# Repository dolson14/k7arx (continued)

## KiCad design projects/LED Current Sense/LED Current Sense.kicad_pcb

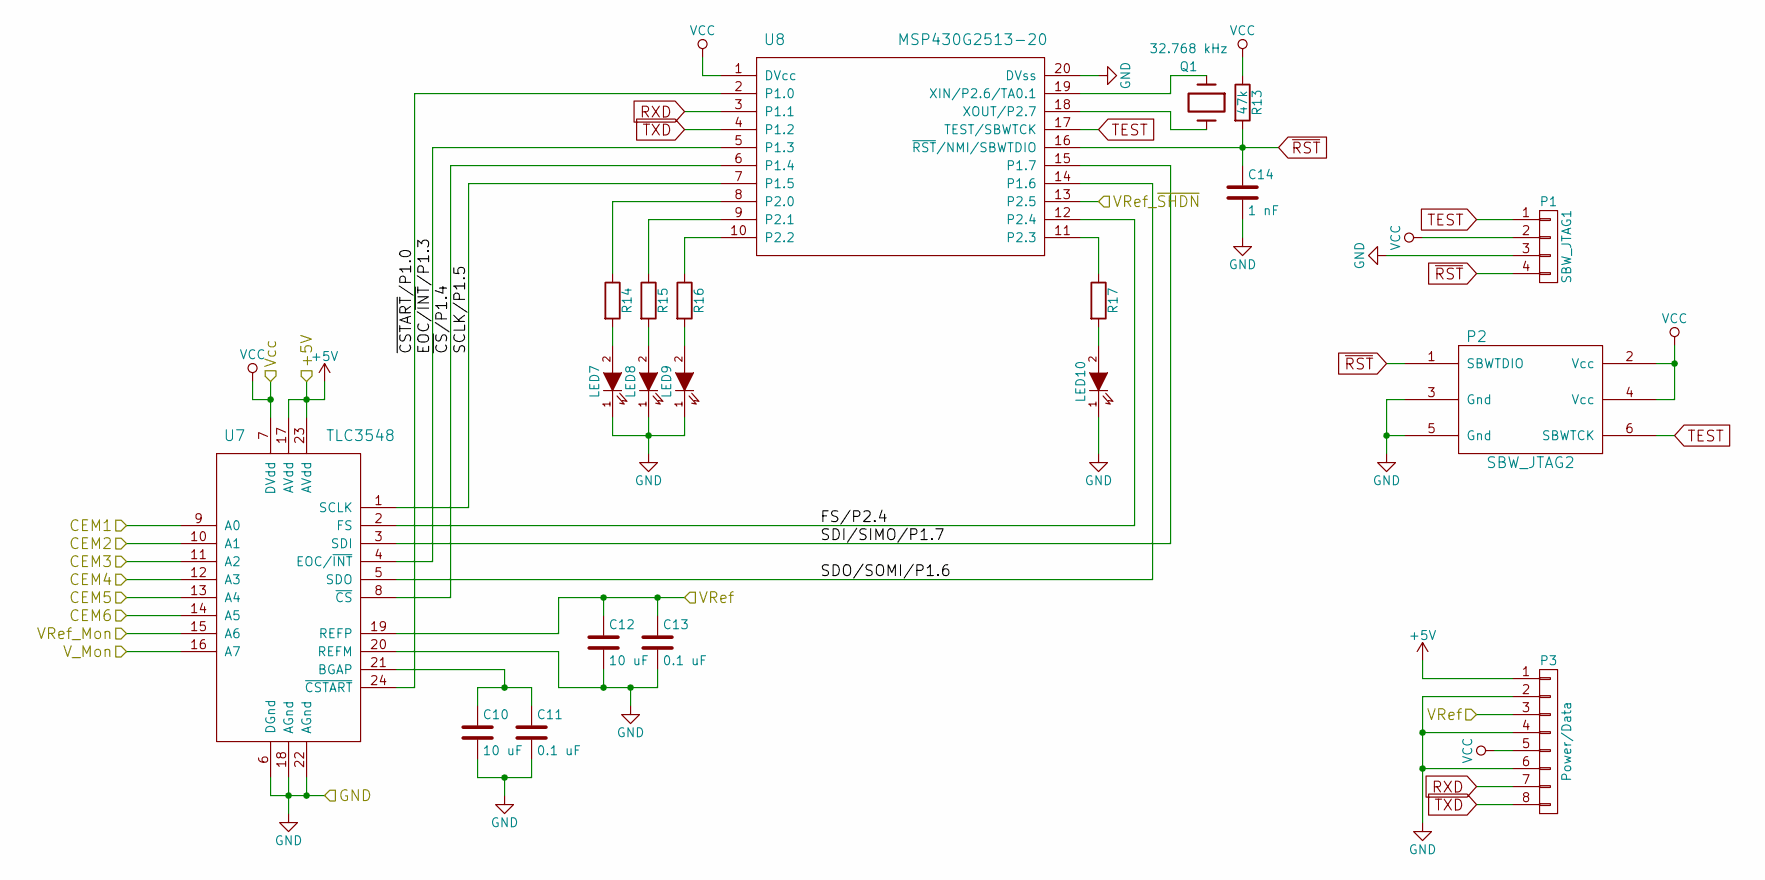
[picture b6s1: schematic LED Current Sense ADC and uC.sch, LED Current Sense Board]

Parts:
C10, C12: 10 uF; C_1206_HandSoldering
C11, C13: 0.1 uF; C_1206_HandSoldering
C14: 1 nF; C_1206_HandSoldering
LED7, LED8, LED9, LED10: LED-0805
P1: SBW_JTAG1; Pin_Header_Straight_1x04
P2: SBW_JTAG2; TC2030-MCP-FP
P3: Power/Data; Pin_Header_Straight_1x08
Q1: 32.768 kHz; Crystal_Round_Vertical_2mm
R13: 47k; R_1206_HandSoldering
R14, R15, R16, R17: R_1206_HandSoldering
U7: TLC3548; SOIC-24_7.5x15.4mm_Pitch1.27mm
U8: MSP430G2513-20; TSSOP-20_4.4x6.5mm_Pitch0.65mm

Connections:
+5V: P3.1, U7.17 (AVdd), U7.23 (AVdd); also elsewhere on the board
/ADC and Microcontroller/EOC/~INT~/P1.3: U7.4 (EOC/~INT), U8.5 (P1.3)
/ADC and Microcontroller/FS/P2.4: U7.2 (FS), U8.12 (P2.4)
/ADC and Microcontroller/SCLK/P1.5: U7.1 (SCLK), U8.7 (P1.5)
/ADC and Microcontroller/SDI/SIMO/P1.7: U7.3 (SDI), U8.15 (P1.7)
/ADC and Microcontroller/SDO/SOMI/P1.6: U7.5 (SDO), U8.14 (P1.6)
/ADC and Microcontroller/VRef: C12.1, C13.1, P3.3, U7.19 (REFP); also elsewhere on the board
/ADC and Microcontroller/~CSTART~/P1.0: U7.24 (~CSTART), U8.2 (P1.0)
/ADC and Microcontroller/~CS~/P1.4: U7.8 (~CS), U8.6 (P1.4)
/High Voltage Interface and Power System/A0: U7.9 (A0); also elsewhere on the board
/High Voltage Interface and Power System/A1: U7.10 (A1); also elsewhere on the board
/High Voltage Interface and Power System/A2: U7.11 (A2); also elsewhere on the board
/High Voltage Interface and Power System/A3: U7.12 (A3); also elsewhere on the board
/High Voltage Interface and Power System/A4: U7.13 (A4); also elsewhere on the board
/High Voltage Interface and Power System/A5: U7.14 (A5); also elsewhere on the board
/High Voltage Interface and Power System/A6: U7.15 (A6); also elsewhere on the board
/High Voltage Interface and Power System/A7: U7.16 (A7); also elsewhere on the board
/High Voltage Interface and Power System/P2.5: U8.13 (P2.5); also elsewhere on the board
GND: C10.2, C11.2, C12.2, C13.2, C14.2, LED7.1 (K), LED8.1 (K), LED9.1 (K), LED10.1 (K), P1.3, P2.3 (Gnd), P2.5 (Gnd), P3.2, P3.4, P3.6, U7.6 (DGnd), U7.18 (AGnd), U7.20 (REFM), U7.22 (AGnd), U8.20 (DVss); also elsewhere on the board
unnamed: C10.1, C11.1, U7.21 (BGAP)
unnamed: LED7.2 (A), R14.2
unnamed: LED8.2 (A), R15.2
unnamed: LED9.2 (A), R16.2
unnamed: LED10.2 (A), R17.2
unnamed: Q1.1, U8.19 (XIN/P2.6/TA0.1)
unnamed: Q1.2, U8.18 (XOUT/P2.7)
unnamed: R14.1, U8.8 (P2.0)
unnamed: R15.1, U8.9 (P2.1)
unnamed: R16.1, U8.10 (P2.2)
unnamed: R17.1, U8.11 (P2.3)
RXD: P3.7, U8.3 (P1.1)
TEST: P1.1, P2.6 (SBWTCK), U8.17 (TEST/SBWTCK)
TXD: P3.8, U8.4 (P1.2)
VCC: P1.2, P2.2 (Vcc), P2.4 (Vcc), P3.5, R13.1, U7.7 (DVdd), U8.1 (DVcc); also elsewhere on the board
~RST: C14.1, P1.4, P2.1 (SBWTDIO), R13.2, U8.16 (~RST~/NMI/SBWTDIO)

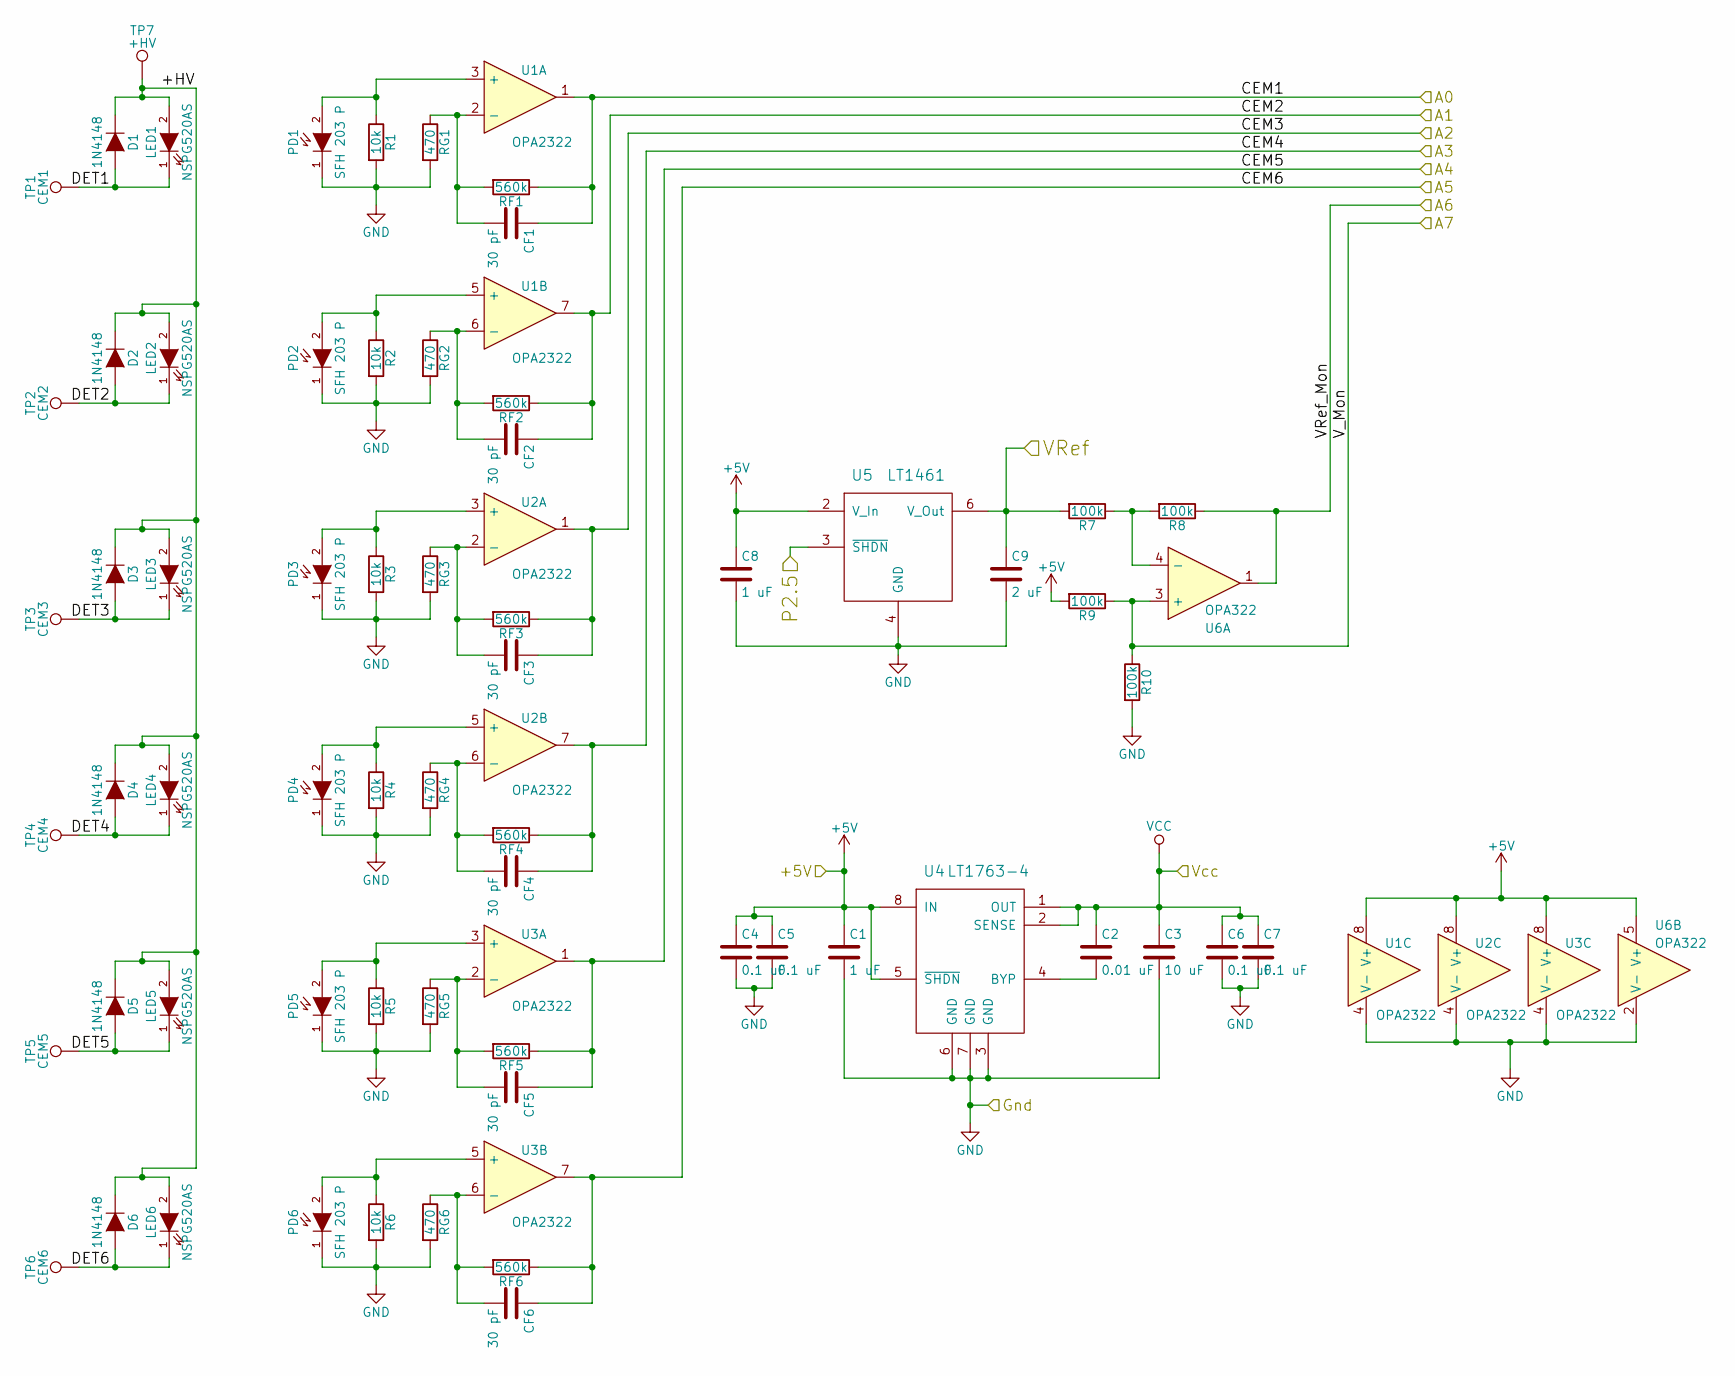
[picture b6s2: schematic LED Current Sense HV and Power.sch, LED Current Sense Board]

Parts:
C1, C8: 1 uF; C_1206_HandSoldering
C2: 0.01 uF; C_1206_HandSoldering
C3: 10 uF; C_1206_HandSoldering
C4, C5, C6, C7: 0.1 uF; C_1206_HandSoldering
C9: 2 uF; C_1206_HandSoldering
CF1, CF2, CF3, CF4, CF5, CF6: 30 pF; C_1206_HandSoldering
D1, D2, D3, D4, D5, D6: 1N4148; Diode_DO-35_SOD27_Horizontal_RM10
LED1, LED2, LED3, LED4, LED5, LED6: NSPG520AS; LED-5MM
PD1, PD2, PD3, PD4, PD5, PD6: SFH 203 P; LED-5MM
R1, R2, R3, R4, R5, R6: 10k; R_1206_HandSoldering
R7, R8, R9, R10: 100k; R_1206_HandSoldering
RF1, RF2, RF3, RF4, RF5, RF6: 560k; R_1206_HandSoldering
RG1, RG2, RG3, RG4, RG5, RG6: 470; R_1206_HandSoldering
TP1: CEM1; No.2N
TP2: CEM2; No.2N
TP3: CEM3; No.2N
TP4: CEM4; No.2N
TP5: CEM5; No.2N
TP6: CEM6; No.2N
TP7: +HV; No.2N
U1, U2, U3: OPA2322; SOIC-8_3.9x4.9mm_Pitch1.27mm
U4: LT1763-4; SOIC-8_3.9x4.9mm_Pitch1.27mm
U5: LT1461; SOIC-8_3.9x4.9mm_Pitch1.27mm
U6: OPA322; SOT-23-5

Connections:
+5V: C1.1, C4.1, C5.1, C8.1, R9.2, U1.8 (V+), U2.8 (V+), U3.8 (V+), U4.5 (~SHDN), U4.8 (IN), U5.2 (V_In), U6.5 (V+); also elsewhere on the board
/ADC and Microcontroller/VRef: C9.1, R7.2, U5.6 (V_Out); also elsewhere on the board
/High Voltage Interface and Power System/+HV: D1.1 (K), D2.1 (K), D3.1 (K), D4.1 (K), D5.1 (K), D6.1 (K), LED1.2 (A), LED2.2 (A), LED3.2 (A), LED4.2 (A), LED5.2 (A), LED6.2 (A), TP7.1
/High Voltage Interface and Power System/A0: CF1.1, RF1.1, U1.1; also elsewhere on the board
/High Voltage Interface and Power System/A1: CF2.1, RF2.1, U1.7; also elsewhere on the board
/High Voltage Interface and Power System/A2: CF3.1, RF3.1, U2.1; also elsewhere on the board
/High Voltage Interface and Power System/A3: CF4.1, RF4.1, U2.7; also elsewhere on the board
/High Voltage Interface and Power System/A4: CF5.1, RF5.1, U3.1; also elsewhere on the board
/High Voltage Interface and Power System/A5: CF6.1, RF6.1, U3.7; also elsewhere on the board
/High Voltage Interface and Power System/A6: R8.1, U6.1; also elsewhere on the board
/High Voltage Interface and Power System/A7: R9.1, R10.1, U6.3 (+); also elsewhere on the board
/High Voltage Interface and Power System/P2.5: U5.3 (~SHDN); also elsewhere on the board
GND: C1.2, C3.2, C4.2, C5.2, C6.2, C7.2, C8.2, C9.2, PD1.1 (K), PD2.1 (K), PD3.1 (K), PD4.1 (K), PD5.1 (K), PD6.1 (K), R1.2, R2.2, R3.2, R4.2, R5.2, R6.2, R10.2, RG1.2, RG2.2, RG3.2, RG4.2, RG5.2, RG6.2, U1.4 (V-), U2.4 (V-), U3.4 (V-), U4.3 (GND), U4.6 (GND), U4.7 (GND), U5.4 (GND), U6.2 (V-); also elsewhere on the board
unnamed: C2.2, U4.4 (BYP)
unnamed: CF1.2, RF1.2, RG1.1, U1.2 (-)
unnamed: CF2.2, RF2.2, RG2.1, U1.6 (-)
unnamed: CF3.2, RF3.2, RG3.1, U2.2 (-)
unnamed: CF4.2, RF4.2, RG4.1, U2.6 (-)
unnamed: CF5.2, RF5.2, RG5.1, U3.2 (-)
unnamed: CF6.2, RF6.2, RG6.1, U3.6 (-)
unnamed: D1.2 (A), LED1.1 (K), TP1.1
unnamed: D2.2 (A), LED2.1 (K), TP2.1
unnamed: D3.2 (A), LED3.1 (K), TP3.1
unnamed: D4.2 (A), LED4.1 (K), TP4.1
unnamed: D5.2 (A), LED5.1 (K), TP5.1
unnamed: D6.2 (A), LED6.1 (K), TP6.1
unnamed: PD1.2 (A), R1.1, U1.3 (+)
unnamed: PD2.2 (A), R2.1, U1.5 (+)
unnamed: PD3.2 (A), R3.1, U2.3 (+)
unnamed: PD4.2 (A), R4.1, U2.5 (+)
unnamed: PD5.2 (A), R5.1, U3.3 (+)
unnamed: PD6.2 (A), R6.1, U3.5 (+)
unnamed: R7.1, R8.2, U6.4 (-)
VCC: C2.1, C3.1, C6.1, C7.1, U4.1 (OUT), U4.2 (SENSE); also elsewhere on the board

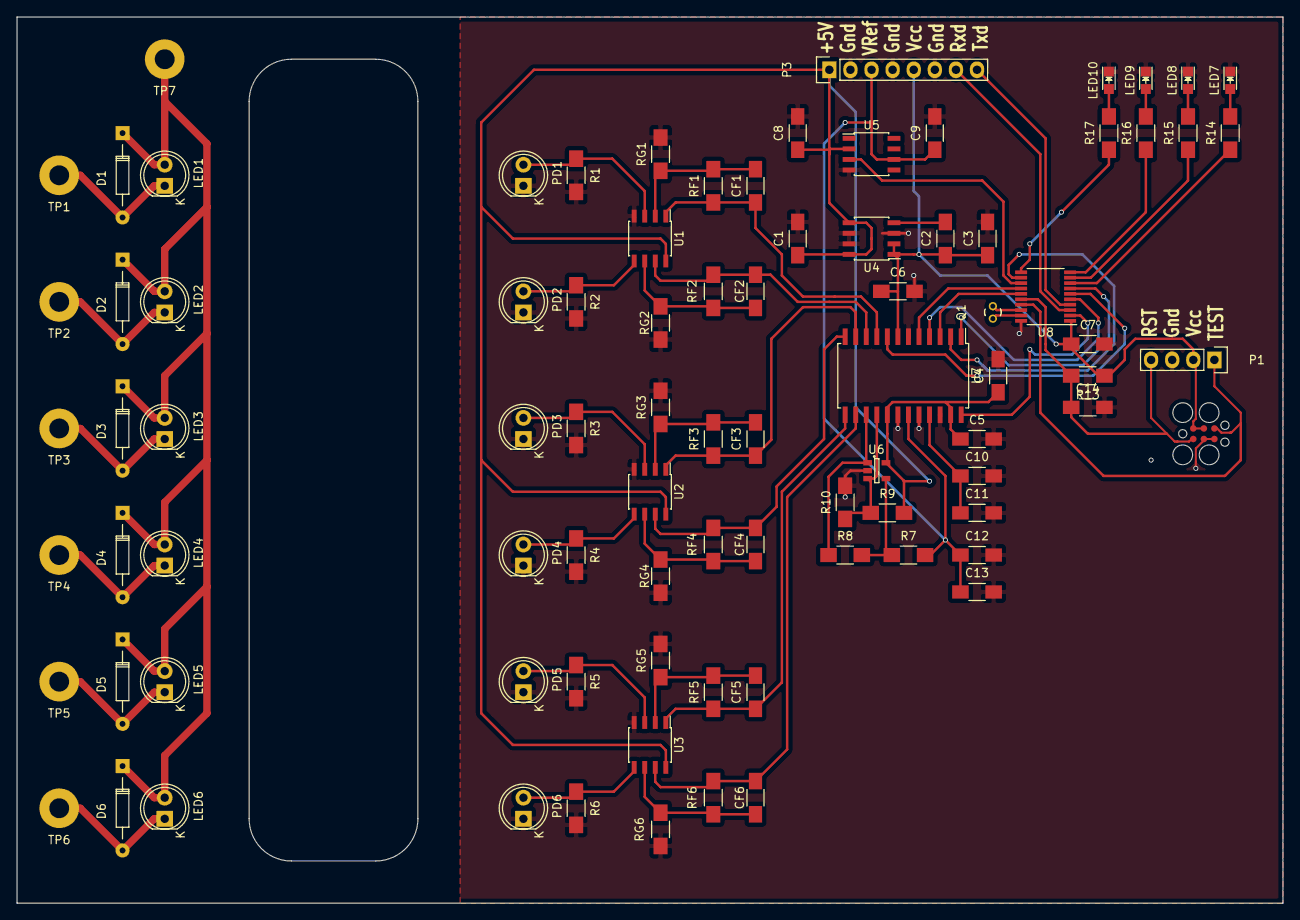
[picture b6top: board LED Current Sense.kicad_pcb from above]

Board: 2 copper layers, 152.4 x 106.7 mm, 88 parts (0 on the bottom side), 56 nets.
